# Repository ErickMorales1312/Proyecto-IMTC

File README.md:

# Proyecto-IMTC
**IoT Project for Autonomous Firefighting and Fire Detection System**

## Structure
This repo consists of the following folders:
1. **Scripts**: This folder is used for programming ESP32 (robot, cloud, detection modules).
2. **KiCad**: Electronic design projects for robot and detection modules, footprints, datasheet, BOM, etc.
3. **Docs**: Word, ppt, excel documents.
4. **Workflow**: Algorithms designed (diagrams, etc).
5. **Test**: Save simple codes for testing components.

**Commits**: 
For better organization, set commits as:
- chore: Updates of tasks
- Test: Testing components, repetitive code useful
- feat: Adding new feature on the project
   
## Step by Step Guide

### Setup
1. **Install Git Bash**
   - Download and install Git Bash from: https://gitforwindows.org/

### Configure Git
   - Set your username and email in Git Bash or command prompt.
       ```bash
        git config --global user.name "Your Name"
        git config --global user.email "your.email@example.com"

**Note** You can refer to this YouTube tutorial for guidance. (https://www.youtube.com/watch?v=8JJ101D3knE)

### Clone Repository
1. **Get the Repository Link**
   - Go to Proyecto-IMTC GitHub Repository.
   - Click on the green "Code" button and copy the HTTP link.

2. **Clone the Repository**
   - Open File Explorer and navigate to the folder where you want to save the repository.
   - Open Git Bash in the selected directory and run the following command:
     ```bash
     git clone <HTTP_LINK>

### Using Command Prompt 
You can use git -h to see more details about each Git instruction. 

## Commits and Create New Branches
### 1. Create a New Branch
   - Open the command prompt, locate the repository folder and run the following command:
     ```bash
     git branch <Name of the new branch>

### 2. **Checkout**
   - Change the main branch to new branch using the following command:
     ```bash
     git checkout <Name of the new branch>
   Then, you can save your work on this branch and commit changes.

### 3. **Commit changes**
   - Add modified files using:
     ```bash
        git add <name of the file> #for a specific file
        git add . #for all updated files
   - Make a commit 
     ```bash
        git commit -m <"name of commit">

### 4. **Push Branch to Remote**
   - At this point, your local changes are stashed temporarily, but to save your changes on the branch, you should push the branch to remote repository, using:
      ```bash
      git push origin <Name of the new branch>

### 5. **Create a PR**
   - Make a PR to merge your changes into main branch.

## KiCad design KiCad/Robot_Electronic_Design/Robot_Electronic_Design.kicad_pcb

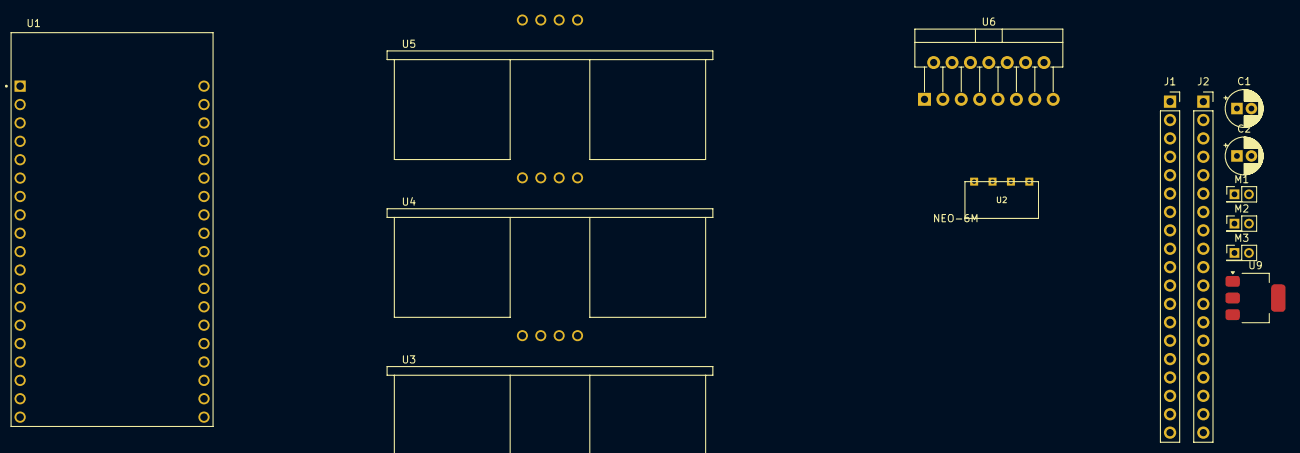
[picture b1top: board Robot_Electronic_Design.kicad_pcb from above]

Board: 2 copper layers, 14 parts (0 on the bottom side), 7 nets, no tracks yet.

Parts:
C1, C2: 10uF; CP_Radial_D5.0mm_P2.00mm
J1, J2: Conn_01x19_Female; PinSocket_1x19_P2.54mm_Vertical
M1, M2: Motor_DC; PinHeader_2x01_P2.00mm_Vertical
M3: Water Pump; PinHeader_2x01_P2.00mm_Vertical
U1: ESP32-DEVKITC-32D; MODULE_ESP32-DEVKITC-32D
U2: NEO-6M
U3, U4, U5: HC-SR04; XCVR_HC-SR04
U6: L298N; TO-220-15_P2.54x2.54mm_StaggerOdd_Lead4.58mm_Vertical
U9: AMS1117-5.0; SOT-223-3_TabPin2

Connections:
/MOTOR_1_OUT1: M1.1 (+), U6.2 (OUT1)
/MOTOR_1_OUT2: M1.2 (-), U6.3 (OUT2)
/MOTOR_2_OUT1: M2.1 (+), U6.13 (OUT3)
/MOTOR_2_OUT2: M2.2 (-), U6.14 (OUT4)
GND: C1.2, C2.2, U3.4 (GND), U4.4 (GND), U5.4 (GND), U6.8 (GND), U9.1 (GND)
VCC: C1.1, U6.4 (Vs), U9.3 (VI)
Vin: C2.1, U3.1 (VCC), U4.1 (VCC), U5.1 (VCC), U6.9 (Vss), U9.2 (VO)

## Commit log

2025-02-21 chore: Initial commit
    Create directory
2025-03-02 Sync files with oneDrive
2025-03-02 Add KiCad Projects
2025-03-09 chore: Create Arduino Project
    - HTML add to library (html.h, html.cpp)
2025-04-06 Update Kicad Files
2025-04-06 chore: Update Arduino Script
2025-04-06 fix: Arduino Script
2025-04-06 fix: Adding delay time for buttons
2025-04-06 chore: Update Arduino file
2025-04-06 chore: Update ino file
2025-04-11 feat: Adding GPS module
2025-05-07 test: DC Motors
2025-05-07 fix: Motors DC ino file
2025-05-07 chore: Update DC Motors ino file
2025-05-07 chore: update DC Motors script
2025-05-08 Fix: Right Movement DC Motors script
2025-05-08 chore: Adding GPS in web server
2025-05-10 feat: Adding Compass Calibration
2025-05-15 Adding libraries
2025-05-26 Adding Scripts
2025-05-26 fix VehicleScript
